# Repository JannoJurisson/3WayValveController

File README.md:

# 3WayValveController

Atmega328 based 3-way valve controller using a MG995 servo motor

A standalone controller using a Dallas DS18B20 sensors as input and MG995 servo motor as output that moves 3-way valve. Two end switches help to position the valve.
NRF24L01 is used to log temperature to Thingspeak

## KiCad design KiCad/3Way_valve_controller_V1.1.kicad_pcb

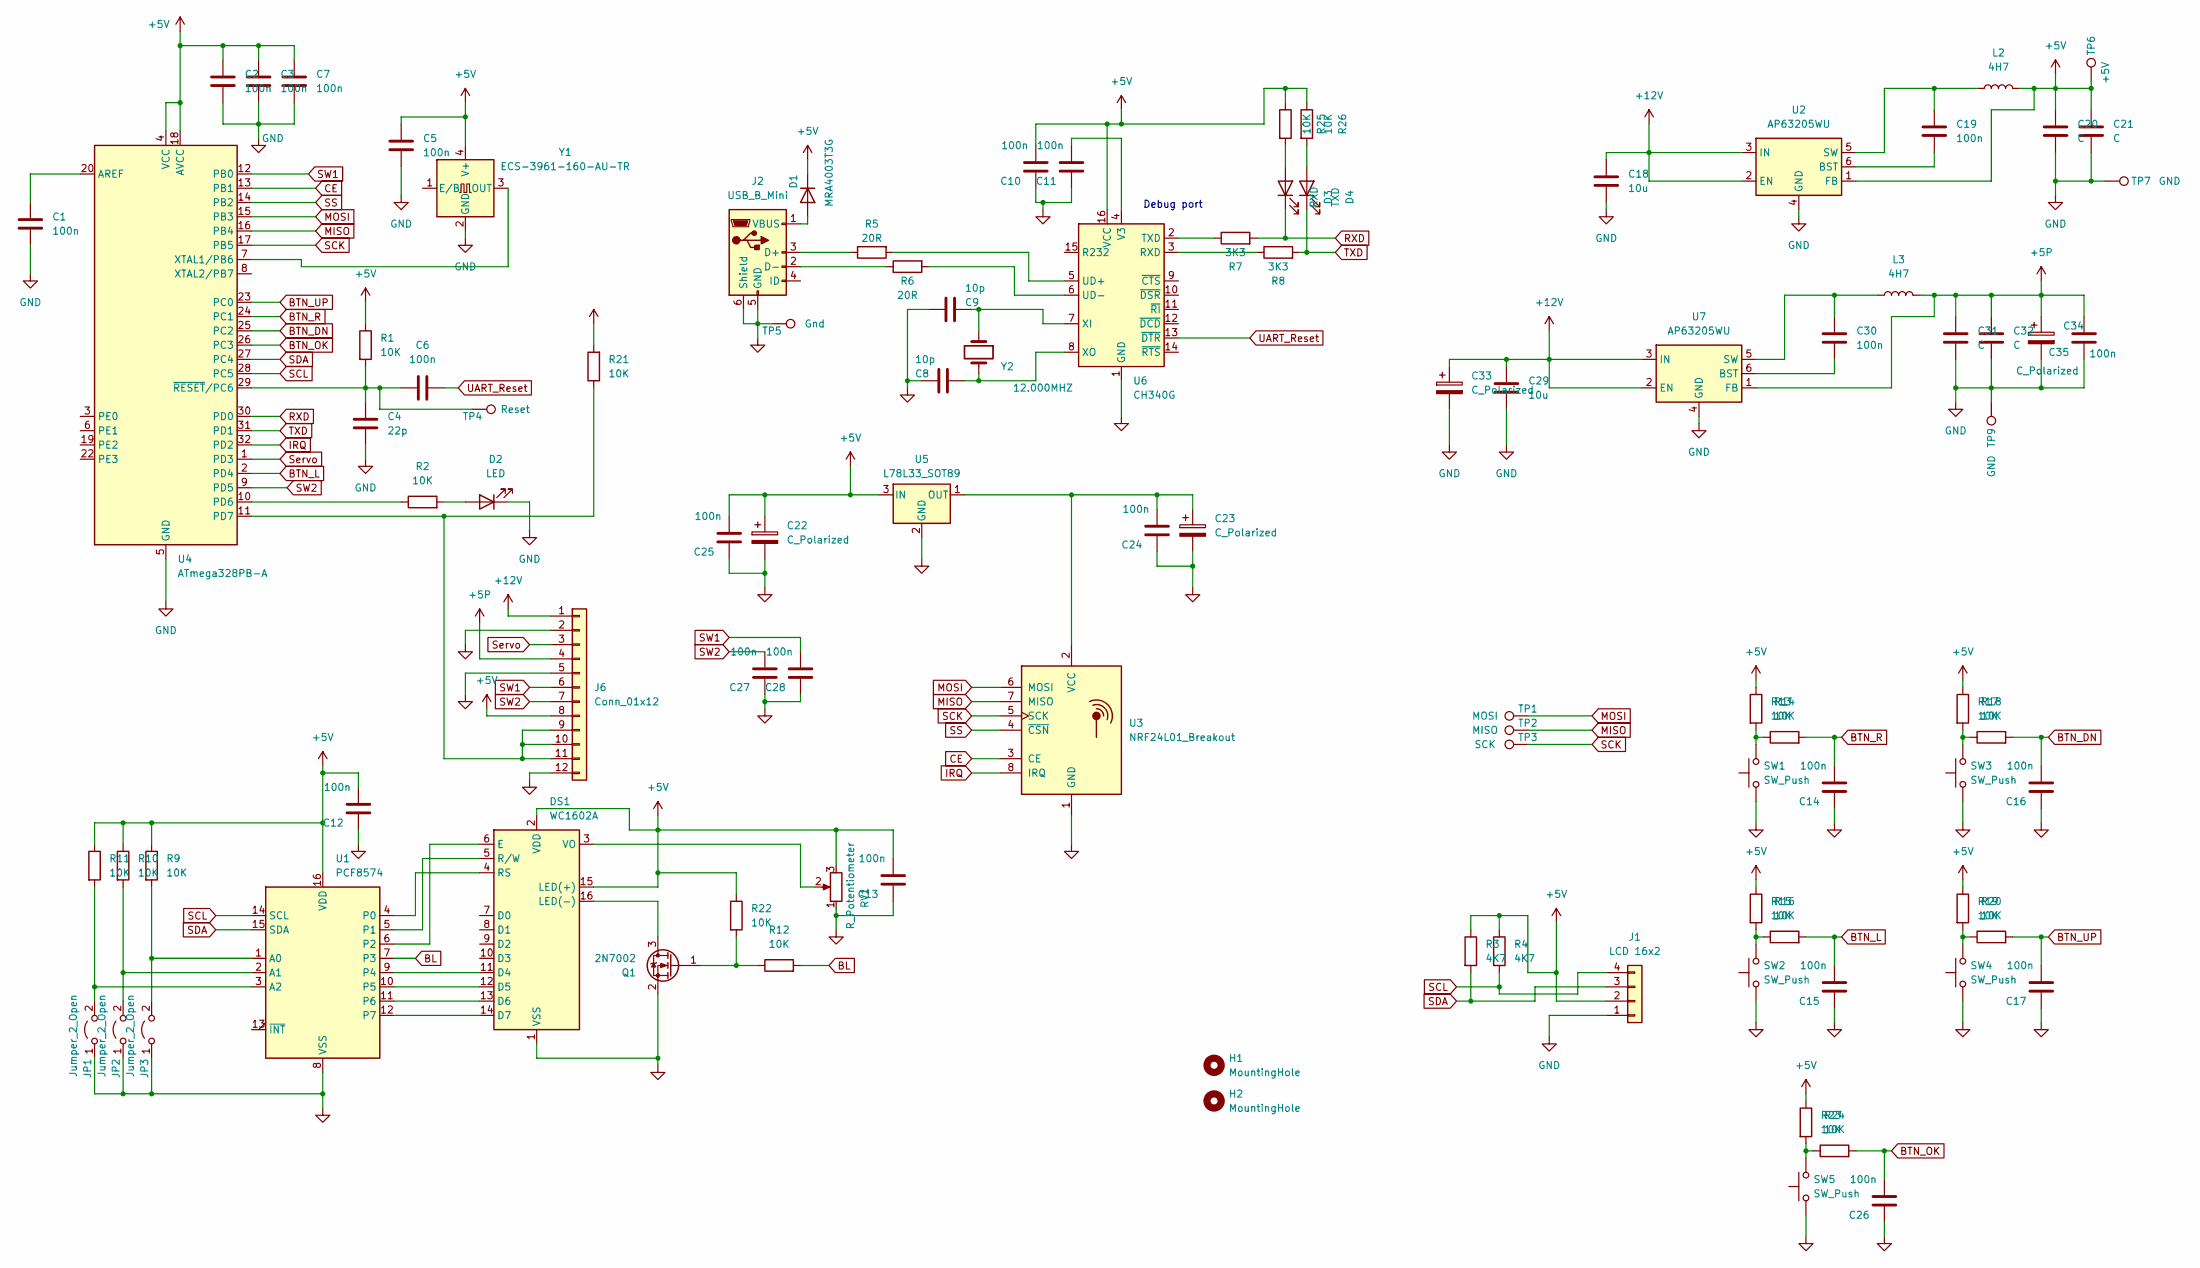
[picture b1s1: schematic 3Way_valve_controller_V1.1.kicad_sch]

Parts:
C1, C2, C3, C5, C6, C7, C14, C15, C16, C17, C19, C26, C30: 100n; C_0603_1608Metric
C4: 22p; C_0603_1608Metric
C8, C9: 10p; C_0603_1608Metric_Pad1.08x0.95mm_HandSolder
C10, C11, C12, C13, C24, C25, C27, C28, C35: 100n; C_0603_1608Metric_Pad1.08x0.95mm_HandSolder
C18, C29: 10u; C_1206_3216Metric
C20, C21, C31, C32: C; C_1206_3216Metric
C22, C23, C33, C34: C_Polarized; CP_Elec_10x10
D1: MRA4003T3G; D_SMA
D2: LED; LED_1206_3216Metric
D3: RXD; LED_1206_3216Metric
D4: TXD; LED_1206_3216Metric
DS1: WC1602A
H1, H2: MountingHole; MountingHole_3.2mm_M3
J1: LCD 16x2; PinHeader_1x04_P2.54mm_Vertical
J2: USB_B_Mini; JLCPCB_C404968_Micro_USB
J6: Conn_01x12; PhoenixContact_MCV_1,5_12-GF-3.5_1x12_P3.50mm_Vertical_Thre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
JP1, JP2, JP3: Jumper_2_Open; SolderJumper-2_P1.3mm_Open_Pad1.0x1.5mm
L2, L3: 4H7; L_Bourns_SRP7028A_7.3x6.6mm
Q1: 2N7002; SOT-23
R1, R2, R9, R10, R11, R12, R13, R14, R15, R16, R17, R18, R19, R20, R21, R22, R23, R24, R25, R26: 10K; R_0603_1608Metric
R3, R4: 4K7; R_0603_1608Metric
R5, R6: 20R; R_0603_1608Metric_Pad0.98x0.95mm_HandSolder
R7, R8: 3K3; R_0603_1608Metric_Pad0.98x0.95mm_HandSolder
RV1: R_Potentiometer; Potentiometer_Vishay_T73YP_Vertical
SW1, SW2, SW3, SW4, SW5: SW_Push; SW_PUSH_6mm
TP1: MOSI; TestPoint_Pad_D1.5mm
TP2: MISO; TestPoint_Pad_D1.5mm
TP3: SCK; TestPoint_Pad_D1.5mm
TP4: Reset; TestPoint_Pad_D1.5mm
TP5: Gnd; TestPoint_Pad_D1.5mm
TP6: +5V; TestPoint_Pad_D1.5mm
TP7, TP9: GND; TestPoint_Pad_D1.5mm
U1: PCF8574; SOIC-16W_7.5x10.3mm_P1.27mm
U2, U7: AP63205WU; TSOT-23-6
U3: NRF24L01_Breakout; nRF24L01_Breakout
U4: ATmega328PB-A; TQFP-32_7x7mm_P0.8mm
U5: L78L33_SOT89; SOT-89-3
U6: CH340G; SOIC-16_3.9x9.9mm_P1.27mm
Y1: ECS-3961-160-AU-TR; Oscillator_SMD_EuroQuartz_XO53-4Pin_5.0x3.2mm
Y2: 12.000MHZ; Crystal_SMD_5032-2Pin_5.0x3.2mm

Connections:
+5P: C31.1, C32.1, C34.1, C35.2, J6.4, L3.2, U7.1 (FB)
+5V: C2.2, C3.2, C5.2, C7.2, C10.2, C12.2, C13.2, C20.1, C21.1, C22.1, C25.2, D1.1 (K), DS1.2 (VDD), DS1.15 (LED(+)), J1.2, J6.8, L2.2, R1.1, R3.1, R4.1, R9.1, R10.1, R11.1, R13.1, R15.1, R17.1, R19.1, R21.2, R22.1, R23.1, R25.1, R26.1, RV1.3, TP6.1, U1.16 (VDD), U2.1 (FB), U4.4 (VCC), U4.18 (AVCC), U5.3 (IN), U6.16 (VCC), Y1.4 (V+)
+12V: C18.1, C29.1, C33.1, J6.1, U2.2 (EN), U2.3 (IN), U7.2 (EN), U7.3 (IN)
BL: R12.2, U1.7 (P3)
BTN_DN: C16.2, R18.2, U4.25 (PC2)
BTN_L: C15.2, R16.2, U4.2 (PD4)
BTN_OK: C26.2, R24.2, U4.26 (PC3)
BTN_R: C14.2, R14.2, U4.24 (PC1)
BTN_UP: C17.2, R20.2, U4.23 (PC0)
CE: U3.3 (CE), U4.13 (PB1)
GND: C1.1, C2.1, C3.1, C4.1, C5.1, C7.1, C8.2, C9.2, C10.1, C11.1, C12.1, C13.1, C14.1, C15.1, C16.1, C17.1, C18.2, C20.2, C21.2, C22.2, C23.2, C24.1, C25.1, C26.1, C27.1, C28.1, C29.2, C31.2, C32.2, C33.2, C34.2, C35.1, D2.1 (K), DS1.1 (VSS), J1.1, J2.5 (GND), J2.6 (Shield), J6.2, J6.5, J6.12, JP1.1 (A), JP2.1 (A), JP3.1 (A), Q1.2 (S), RV1.1, SW1.1, SW2.1, SW3.1, SW4.1, SW5.1, TP5.1, TP7.1, TP9.1, U1.8 (VSS), U2.4 (GND), U3.1 (GND), U4.5 (GND), U4.21 (GND), U5.2 (GND), U6.1 (GND), U7.4 (GND), Y1.2 (GND)
IRQ: U3.8 (IRQ), U4.32 (PD2)
MISO: TP2.1, U3.7 (MISO), U4.16 (PB4)
MOSI: TP1.1, U3.6 (MOSI), U4.15 (PB3)
unnamed: D1.2 (A), J2.1 (VBUS)
unnamed: D2.2 (A), R2.2
unnamed: D3.2 (A), R25.2
unnamed: D4.2 (A), R26.2
unnamed: DS1.11 (D4), U1.9 (P4)
unnamed: DS1.12 (D5), U1.10 (P5)
unnamed: DS1.13 (D6), U1.11 (P6)
unnamed: DS1.14 (D7), U1.12 (P7)
unnamed: DS1.6 (E), U1.6 (P2)
unnamed: DS1.16 (LED(-)), Q1.3 (D)
unnamed: DS1.4 (RS), U1.4 (P0)
unnamed: DS1.5 (R/W), U1.5 (P1)
unnamed: DS1.3 (VO), RV1.2
unnamed: J2.3 (D+), R5.1
unnamed: J2.2 (D-), R6.1
unnamed: J6.9, J6.10, J6.11, R21.1, U4.11 (PD7)
unnamed: JP1.2 (B), R11.2, U1.3 (A2)
unnamed: JP2.2 (B), R10.2, U1.2 (A1)
unnamed: JP3.2 (B), R9.2, U1.1 (A0)
unnamed: Q1.1 (G), R12.1, R22.2
unnamed: R13.2, R14.1, SW1.2
unnamed: R15.2, R16.1, SW2.2
unnamed: R17.2, R18.1, SW3.2
unnamed: R19.2, R20.1, SW4.2
unnamed: R23.2, R24.1, SW5.2
unnamed: C19.2, U2.6 (BST)
unnamed: C19.1, L2.1, U2.5 (SW)
unnamed: C23.1, C24.2, U3.2 (VCC), U5.1 (OUT)
unnamed: C1.2, U4.20 (AREF)
unnamed: R2.1, U4.10 (PD6)
unnamed: U4.7 (XTAL1/PB6), Y1.3 (OUT)
unnamed: C4.2, C6.1, R1.2, TP4.1, U4.29 (~RESET/PC6)
unnamed: R8.1, U6.3 (RXD)
unnamed: R7.1, U6.2 (TXD)
unnamed: R5.2, U6.5 (UD+)
unnamed: R6.2, U6.6 (UD-)
unnamed: C11.2, U6.4 (V3)
unnamed: C9.1, U6.7 (XI), Y2.1
unnamed: C8.1, U6.8 (XO), Y2.2
unnamed: C30.2, U7.6 (BST)
unnamed: C30.1, L3.1, U7.5 (SW)
RXD: D3.1 (K), R7.2, U4.30 (PD0)
SCK: TP3.1, U3.5 (SCK), U4.17 (PB5)
SCL: J1.4, R4.2, U1.14 (SCL), U4.28 (PC5)
SDA: J1.3, R3.2, U1.15 (SDA), U4.27 (PC4)
SS: U3.4 (~CSN), U4.14 (PB2)
SW1: C28.2, J6.6, U4.12 (PB0)
SW2: C27.2, J6.7, U4.9 (PD5)
Servo: J6.3, U4.1 (PD3)
TXD: D4.1 (K), R8.2, U4.31 (PD1)
UART_Reset: C6.2, U6.13 (~DTR)

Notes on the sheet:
Debug port

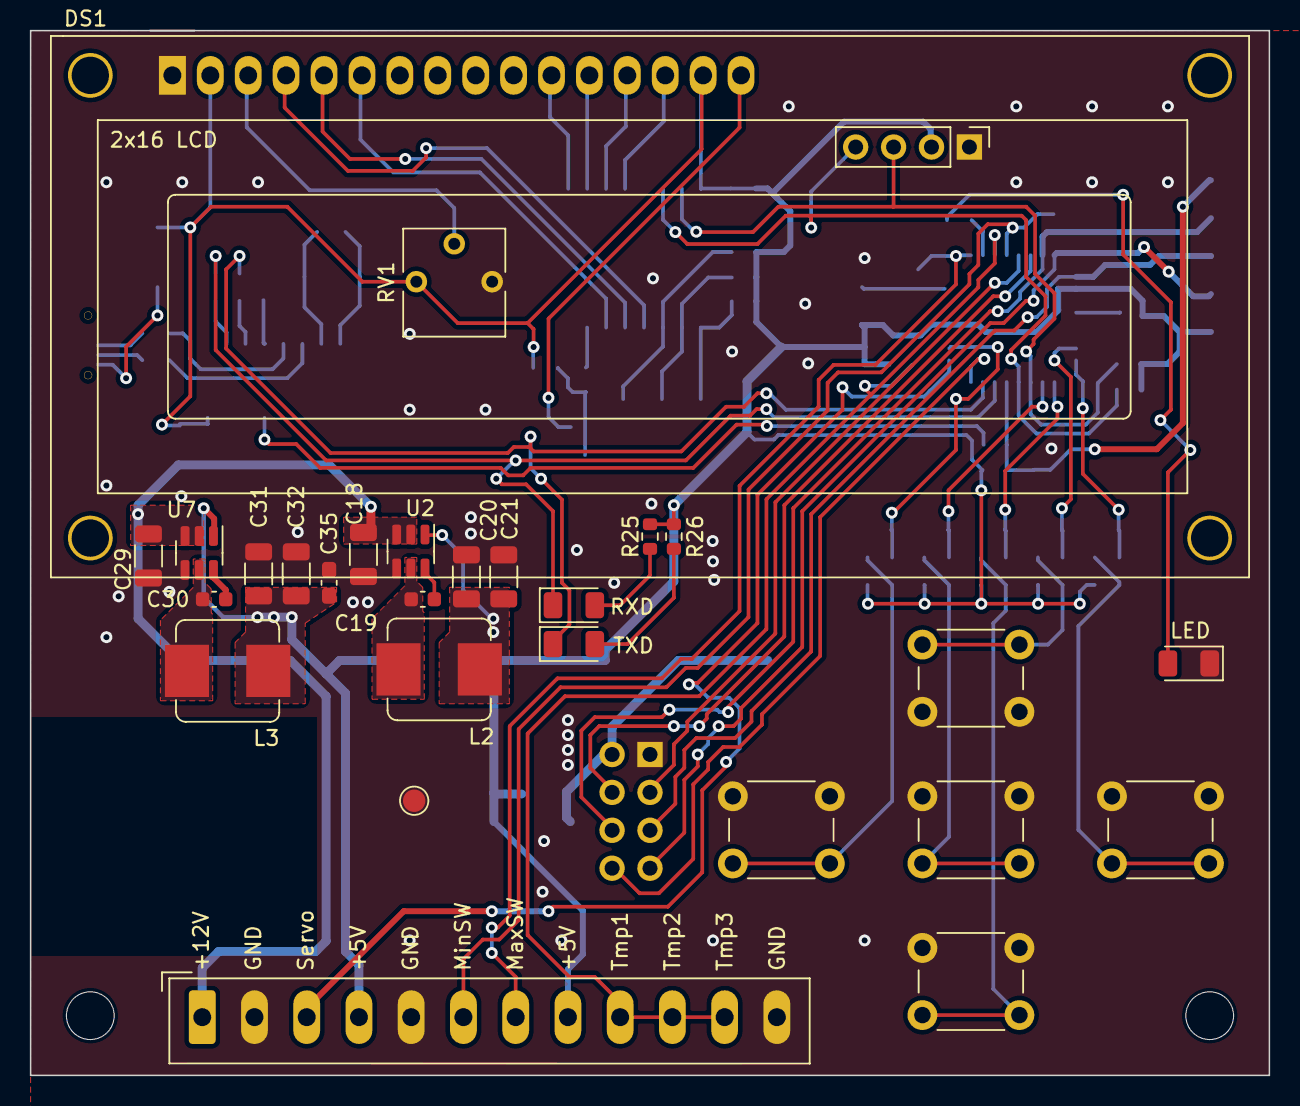
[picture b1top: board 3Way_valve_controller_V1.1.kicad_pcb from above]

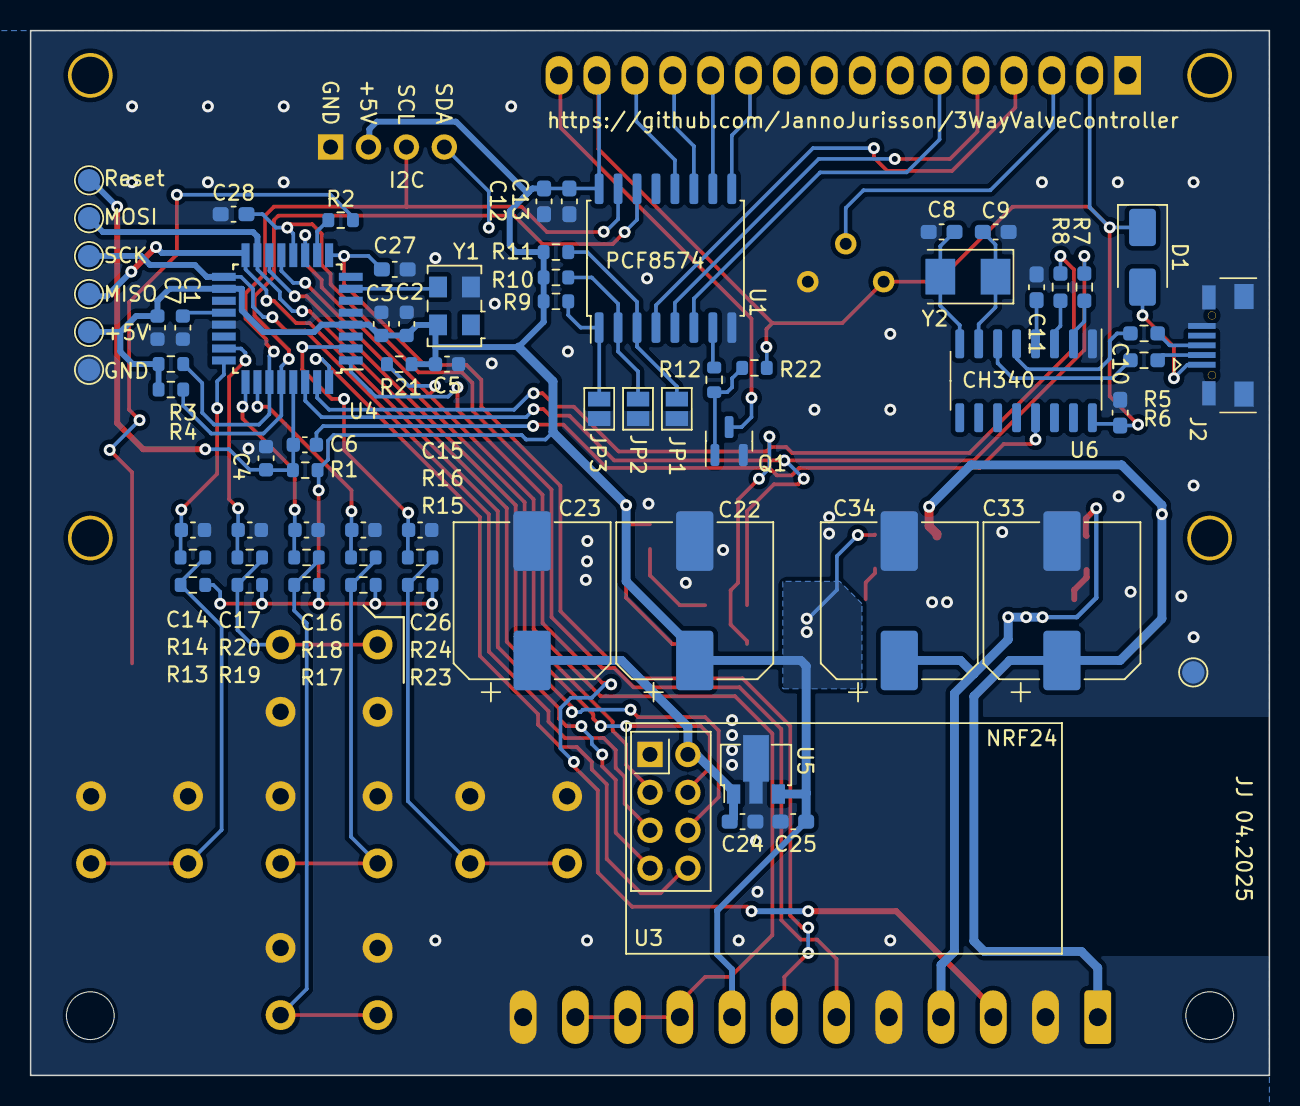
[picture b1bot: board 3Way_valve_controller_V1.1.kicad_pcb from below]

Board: 2 copper layers, 83.0 x 70.0 mm, 100 parts (70 on the bottom side), 65 nets.

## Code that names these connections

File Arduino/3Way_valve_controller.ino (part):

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  TempData data;

#define ONE_WIRE_BUS 7  // Dallas temp sensor data pin
#define SERVO_PIN 3
#define MIN_LIMIT_SWITCH 8  // Active LOW (0 when pressed)
#define MAX_LIMIT_SWITCH 5
#define LED_STATUS 6


#define BTN_UP A0
#define BTN_DOWN A4
#define BTN_LEFT 4
#define BTN_RIGHT A1
#define BTN_OK A3

Servo valveServo;
OneWire oneWire(ONE_WIRE_BUS);
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
  pinMode(MIN_LIMIT_SWITCH, INPUT_PULLUP);
  pinMode(MAX_LIMIT_SWITCH, INPUT_PULLUP);
  pinMode(BTN_UP, INPUT_PULLUP);
  pinMode(BTN_DOWN, INPUT_PULLUP);
  pinMode(BTN_LEFT, INPUT_PULLUP);
  pinMode(BTN_RIGHT, INPUT_PULLUP);
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  }


  valveServo.attach(SERVO_PIN);

  lcd.init();
  lcd.backlight();
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        if (abs(newServoPos - lastServoPos) > 1) {

          if (!servoAttached) {
            valveServo.attach(SERVO_PIN);
            servoAttached = true;
          }

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
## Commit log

2025-05-19 Delete KiCad/3Way_valve_controller.kicad_pcb
    Old version
2025-05-19 Delete KiCad/3Way_valve_controller.kicad_prl
    Old version
2025-05-19 Delete KiCad/3Way_valve_controller.kicad_pro
    Old version
2025-05-19 Delete KiCad/3Way_valve_controller.kicad_sch
    Old version
